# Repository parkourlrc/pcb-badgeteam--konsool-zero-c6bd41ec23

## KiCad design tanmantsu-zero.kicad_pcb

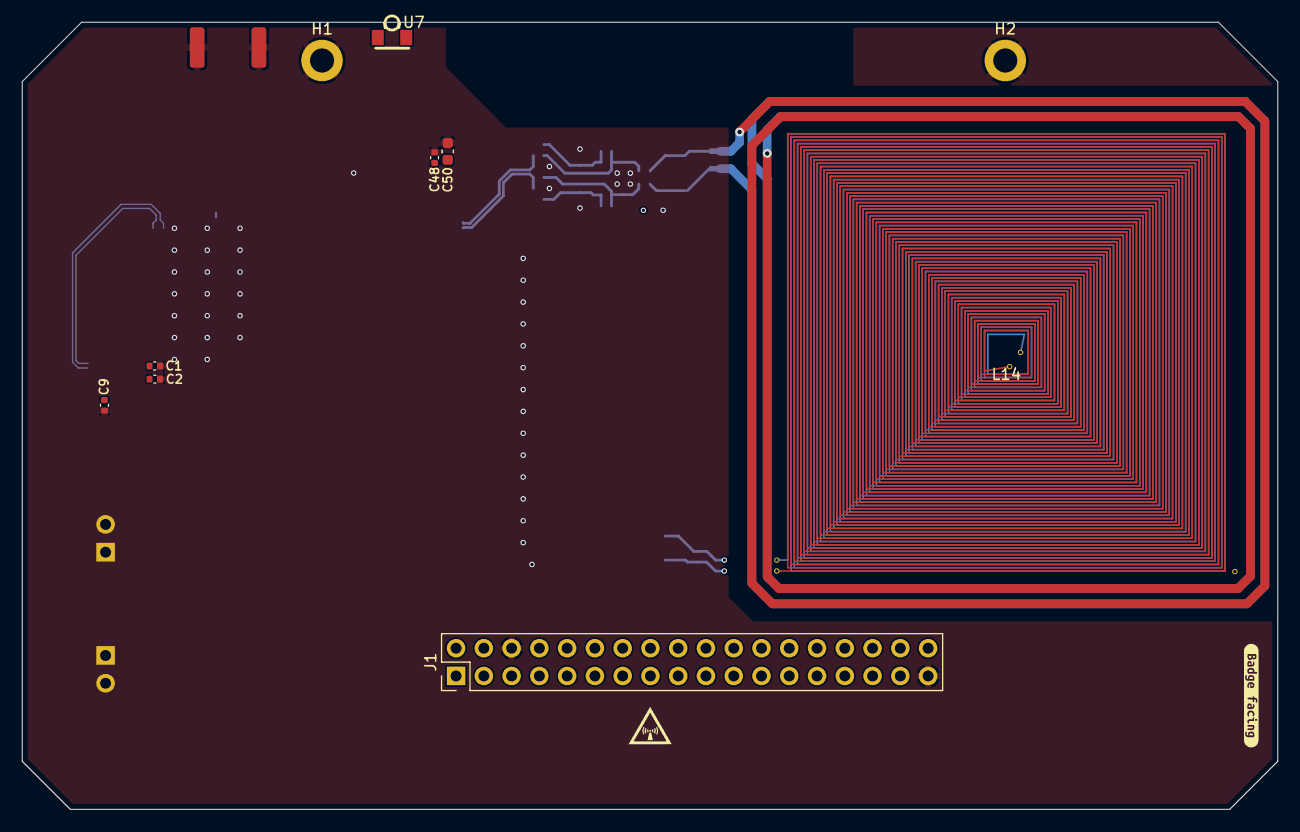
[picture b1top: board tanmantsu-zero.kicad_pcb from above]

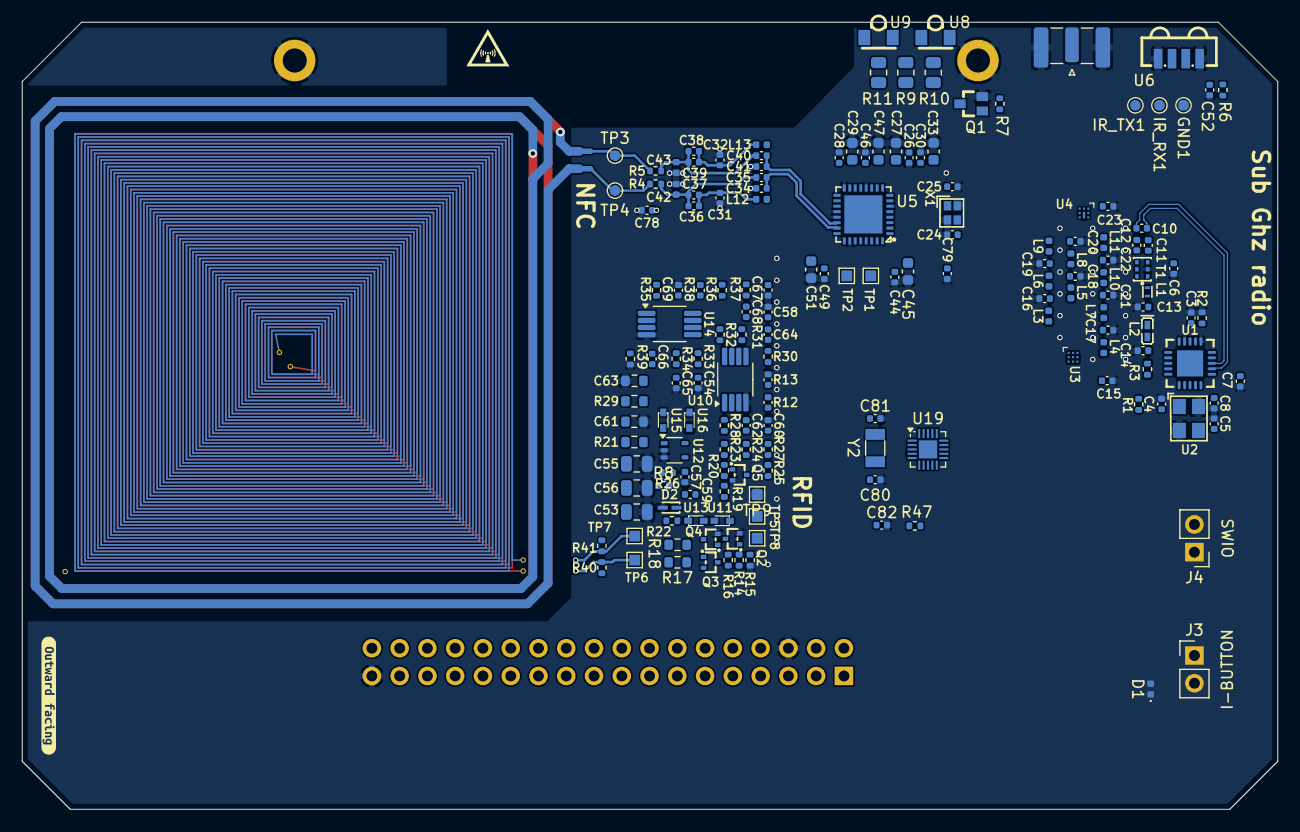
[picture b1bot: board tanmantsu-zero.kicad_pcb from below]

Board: 4 copper layers, 114.8 x 72.0 mm, 182 parts (169 on the bottom side), 105 nets.

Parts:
C1, C2, C3, C6, C7, C8, C9, C52, C54, C57, C58: 100nF; C_0402_1005Metric
C4, C5: 9pF; C_0402_1005Metric
C10: 0.6pF; C_0402_1005Metric
C11, C12, C34, C36, C38, C41, C66, C68, C69: 100pF; C_0402_1005Metric
C13: ??; C_0402_1005Metric
C14: 1.2pF; C_0402_1005Metric
C15, C23, C26, C28, C30, C35, C37, C39, C40, C44, C46, C48, C49, C59, C78, C79: 10nF; C_0402_1005Metric
C16, C19, C20, C64: C_0402_1005Metric
C17, C21: 10pF; C_0402_1005Metric
C18: 8.2pF; C_0402_1005Metric
C22: 22pF; C_0402_1005Metric
C24, C25: 6pF; C_0402_1005Metric
C27, C29, C33, C45, C47, C50, C51: 2.2uF; C_0603_1608Metric
C31, C32: 680pF; C_0402_1005Metric
C42, C43: 62pF; L_0402_1005Metric
C53: 3.9nF; C_0805_2012Metric
C55, C56: C_0805_2012Metric
C60: 1nF; C_0402_1005Metric
C61, C63: C_Small; R_0603_1608Metric
C62: 220nF; C_0402_1005Metric
C65, C67: 4.7nF; C_0402_1005Metric
C80, C81: 22p; C_0402_1005Metric
C82: 100n; C_0402_1005Metric
D1: D_TVS; D_0402_1005Metric
D2: MM5Z33; SOD-523_L1.2-W0.8-LS1.6-RD
GND1: TestPoint; TestPoint_Pad_D1.0mm
H1, H2: Mounting hole; MountingHole_2.2mm_M2_DIN965_Pad
IR_RX1: TestPoint; TestPoint_Pad_D1.0mm
IR_TX1: TestPoint; TestPoint_Pad_D1.0mm
J1: Internal Add-On; PinHeader_2x18_P2.54mm_Vertical
J2: LoRa; SMA_Samtec_SMA-J-P-H-ST-EM1_EdgeMount
J3, J4: Conn_01x02_Pin; PinHeader_1x02_P2.54mm_Vertical
L1: 3.3nH; IND-SMD_L1.0-W0.5
L2: LQG15HS6N8J02D; L0402-RD
L3, L4, L5, L6, L10: 0nH; L_0402_1005Metric
L7: 27nH; L_0402_1005Metric
L8: 2.7nH; L_0402_1005Metric
L9: 56nH; L_0402_1005Metric
L11: 22nH; L_0402_1005Metric
L12, L13: 270nH; L_0402_1005Metric
L14: 400mH; 61-42-rfid-coil
N1, N1#2: Radio-logo; radio-logo
N2: Housing; boards-guide
NT1, NT2: NetTie_2; NetTie-2_SMD_Pad0.5mm
Q1: DMN2058UW-7; SOT-323-3_L2.2-W1.3-P1.30-LS2.1-BR
Q2, Q4: DMN2004TK-7; SOT-523-3_L1.6-W0.8-P1.00-LS1.6-BR
Q3: DMP2004TK-7; SOT-523-3_L1.6-W0.8-P1.00-LS1.6-BR
Q5: DMN5L06TK-7; SOT-523-3_L1.6-W0.8-P1.00-LS1.6-BR
R1, R25: 330; R_0402_1005Metric
R2: 56k; R_0402_1005Metric
R3, R4, R5, R22, R40, R41: 0; R_0402_1005Metric
R6: 10; R_0402_1005Metric
R7: 200; R_0402_1005Metric
R8, R15, R26, R33, R36, R47: 10k; R_0402_1005Metric
R9, R10, R11: 47; R_0805_2012Metric
R12, R13, R38: 33k; C_0402_1005Metric
R14, R23: 100; R_0402_1005Metric
R16, R30, R32, R34, R35, R37: 1k; R_0402_1005Metric
R17, R18: 4.7; R_0603_1608Metric
R19, R20: 220; R_0402_1005Metric
R21: 330k; R_0603_1608Metric
R24: 47k; R_0402_1005Metric
R27: 5.1k; R_0402_1005Metric
R28: 1M; R_0402_1005Metric
R29: 10; R_0603_1608Metric
R31: 4.7k; R_0402_1005Metric
R39: 20k; R_0402_1005Metric
T1: B0310J50100AHF; XFMR-SMD_6P-L2.1-W1.3-P0.65-BL
TP1, TP2: TestPoint; TestPoint_Pad_1.0x1.0mm
TP3, TP4: TestPoint; TestPoint_Pad_D1.0mm
TP5: IRQ; TestPoint_Pad_1.0x1.0mm
TP6: AR1; TestPoint_Pad_1.0x1.0mm
TP7: AR2; TestPoint_Pad_1.0x1.0mm
TP8: DET; TestPoint_Pad_1.0x1.0mm
TP9: GND; TestPoint_Pad_1.0x1.0mm
U1: CC1101RGPR; QFN-20_L4.0-W4.0-P0.5-TL-EP
U2: 27MHz; OSC-SMD_4P-L3.2-W2.5-BL
U3, U4: BGS13S4N9E6327XTSA1; TSNP-9_L1.1-W1.1-P0.40-BL
U5: ST25R3916-AQWT; VFQFPN-32_L5.0-W5.0-P0.50-TL-EP3.5
U6: TSOP75338TR; SENSOR-SMD_TSOP75238TR
U7, U8, U9: VSMY14940; LED-SMD_VSMY14940
U10, U14: LMV358; VSSOP-8_3x3mm_P0.65mm
U11, U13, U15, U16: 1N4148X-TP; SOD-523F_L1.2-W0.8-LS1.7-RD
U12: LMV331IDCKR; SOT-353_SC-70-5
U19: CH32V003F4U6; QFN-20-1EP_3x3mm_P0.4mm_EP1.65x1.65mm
X1: XRCGB27M120F3M00R0; CRYSTAL-SMD_4P-L2.0-W1.6-BL-B
Y2: 32.768KHz; Crystal_SMD_3215-2Pin_3.2x1.5mm
kibuzzard-672F417C: G***; kibuzzard-672F417C
kibuzzard-672F4776: G***; kibuzzard-672F4776

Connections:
+1.65V: R28.2, R30.1, U10.6 (-), U10.7, U14.3 (+), U14.5 (+)
+3.3V: C1.1, C3.1, C6.1, C7.1, C8.1, C9.1, C15.1, C23.1, C26.1, C27.1, C28.1, C29.1, C61.1, C78.1, C79.1, C82.1, J1.8, J1.33, R6.1, R9.1, R10.1, R11.1, R26.1, R29.1, R47.1, U1.4 (DVDD), U1.9 (AVDD), U1.11 (AVDD), U1.14 (AVDD), U1.15 (AVDD), U1.18 (DGUARD), U3.7 (VDD), U4.7 (VDD), U5.1 (VDD_IO), U5.8 (VDD), U5.10 (VDD_TX), U19.6 (VDD)
+3.3VA: C54.2, C57.2, C58.2, C63.1, R12.1, R29.2, U10.8 (V+), U12.5 (V+), U14.8 (V+), U15.1 (C)
+5V: Q3.3 (D), R16.1, R24.1
/NFC block/AGDC: C49.1, C51.1, U5.24 (AGDC)
/NFC block/RFI_N: C34.1, C35.2, U5.23 (RFI2)
/NFC block/RFI_P: C40.1, C41.2, U5.22 (RFI1)
/NFC block/RFO1: L12.1, U5.13 (RFO1)
/NFC block/RFO2: L13.1, U5.15 (EFO2)
/NFC block/VDD_A: C30.1, C33.1, U5.7 (VDD_A)
/NFC block/VDD_AM: C48.1, C50.1, U5.11 (VDD_AM)
/NFC block/VDD_D: C44.1, C45.1, U5.3 (VDD_D)
/NFC block/VDD_DR: C46.1, C47.1, U5.9 (VDD_RF), U5.14 (VDD_DR)
/sub-GHz-radio/Antenna balance/ANT_OUT: J2.1 (In), U4.4 (RFin)
/sub-GHz-radio/Antenna balance/RF_IN: R3.2, U3.4 (RFin)
/sub-GHz-radio/RF-Balance/RF_N: C10.1, C11.1, U1.13 (RF_N)
/sub-GHz-radio/RF-Balance/RF_P: C10.2, C12.1, U1.12 (RF_P)
E0: J1.11, U1.3 (GDO2)
E1: J1.12, R1.1
E3: J1.14, U5.29 (BSS)
E4: J1.15, J4.2, R47.2, U19.15 (PD1)
E9: IR_RX1.1, J1.25, U6.3 (OUT)
E10: IR_TX1.1, J1.23, R7.1
GND: C1.2, C2.1, C3.2, C4.2, C5.2, C6.2, C7.2, C8.2, C9.2, C13.2, C14.2, C15.2, C16.1, C17.2, C18.2, C19.1, C20.2, C21.2, C22.2, C23.2, C24.2, C25.1, C26.2, C27.2, C28.2, C29.2, C30.2, C31.2, C32.1, C33.2, C34.2, C41.1, C42.2, C43.1, C44.2, C45.2, C46.2, C47.2, C48.2, C49.2, C50.2, C51.2, C52.2, C53.2, C54.1, C55.2, C56.2, C57.1, C58.1, C60.2, C61.2, C63.2, C65.2, C67.2, C69.1, C78.2, C79.2, C80.2, C81.2, C82.2, D1.1 (A1), D2.2 (A), GND1.1, H1.1, H2.1, J1.6, J1.35, J2.2 (Ext), J3.1, J4.1, Q1.2 (S), Q2.2 (S), Q4.2 (S), Q5.2 (S), R2.1, R8.2, R13.2, R15.2, R39.2, T1.2 (GND), TP9.1, U1.16 (GND), U1.19 (GND), U1.21 (EP), U2.2 (GND), U2.4 (GND), U3.6 (DGND), U3.9 (GND), U4.6 (DGND), U4.9 (GND), U5.6 (GND_D), U5.12 (GND_DR), U5.16 (GND_DR), U5.20 (I2C_EN), U5.21 (VSS), U5.26 (GND_A), U6.1 (GND), U6.4 (GND), U10.4 (V-), U12.2 (V-), U12.3 (-), U14.4 (V-), U16.1 (C), U19.4 (VSS), U19.21 (VSS), X1.2 (GND), X1.4 (GND)
IBTN: D1.2 (A2), J3.2, R23.1
INT_SCL: J1.9, U19.9 (PC2)
INT_SDA: J1.10, U19.8 (PC1)
NFC_ANT: NT1.2, NT2.1
NFC_IRQ: TP5.1, U5.27 (IRQ), U11.2 (A), U19.20 (PD6)
unnamed: C11.2, T1.3 (Balanced)
unnamed: C12.2, T1.4 (Balanced)
unnamed: C13.1, L1.2, L2.1
unnamed: C14.1, L2.2, R3.1
unnamed: C16.2, L3.2, L6.1
unnamed: C17.1, L4.2, L7.1
unnamed: C18.1, L5.2, L8.1
unnamed: C19.2, L6.2, L9.1
unnamed: C21.1, L7.2, L10.1
unnamed: C22.1, L10.2, L11.1
unnamed: C31.1, C36.1, C37.2, L12.2
unnamed: C32.2, C38.2, C39.2, L13.2
unnamed: C35.1, C36.2, C37.1, C42.1, R4.1
unnamed: C38.1, C39.1, C40.2, C43.2, R5.1
unnamed: C53.1, C55.1, C56.1, R21.1, R22.1, R41.1
unnamed: C59.2, R23.2, R24.2
unnamed: C60.1, C62.1, R27.2
unnamed: C64.2, R31.2, R32.1, U10.1
unnamed: C65.1, R32.2, R33.2, R34.2
unnamed: C66.2, R33.1, R35.1, U14.1
unnamed: C67.1, R35.2, R36.2, R37.2
unnamed: C68.2, R36.1, R38.1, U14.7
unnamed: C59.1, D2.1 (K), R25.2, R27.1, TP8.1, U13.1 (C)
unnamed: L14.1, R40.1, TP6.1
unnamed: L14.2, R41.2, TP7.1
unnamed: NT1.1, R5.2, TP4.1
unnamed: NT2.2, R4.2, TP3.1
unnamed: Q1.3 (D), U7.1 (C), U8.1 (C), U9.1 (C)
unnamed: Q1.1 (G), R7.2, R8.1
unnamed: Q2.3 (D), Q3.1 (G), Q4.1 (G), R16.2
unnamed: Q2.1 (G), R14.2, R15.1
unnamed: Q3.2 (S), R17.1
unnamed: Q4.3 (D), R18.2
unnamed: Q5.3 (D), R25.1
unnamed: Q5.1 (G), R20.2
unnamed: R17.2, R18.1, R40.2
unnamed: L1.1, T1.1 (Unbalanced)
unnamed: C2.2, U1.5 (DCOUPL)
unnamed: R1.2, U1.6 (GDO0(ATEST))
unnamed: R2.2, U1.17 (RBIAS)
unnamed: C4.1, U1.8 (XOSC_Q1), U2.1
unnamed: C5.1, U1.10 (XOSC_Q2), U2.3
unnamed: L3.1, U3.3 (RF1)
unnamed: L4.1, U3.5 (RF2)
unnamed: L5.1, U3.2 (RF3)
unnamed: L9.2, U4.3 (RF1)
unnamed: L11.2, U4.5 (RF2)
unnamed: C20.1, L8.2, U4.2 (RF3)
unnamed: TP2.1, U5.25 (CSI)
unnamed: TP1.1, U5.2 (CSO)
unnamed: C25.2, U5.5 (XTI), X1.1
unnamed: C24.1, U5.4 (XTO), X1.3
unnamed: C52.1, R6.2, U6.2 (+VS)
unnamed: R9.2, U7.2 (A)
unnamed: R10.2, U8.2 (A)
unnamed: R11.2, U9.2 (A)
unnamed: C62.2, R28.1, U10.3 (+), U15.2 (A), U16.2 (A)
unnamed: C64.1, R30.2, R31.1, U10.2 (-)
unnamed: R12.2, R13.1, U10.5 (+)
unnamed: R19.2, R20.1, U11.1 (C)
unnamed: R21.2, U12.1 (+)
unnamed: R22.2, U13.2 (A)
unnamed: C66.1, R34.1, U14.2 (-)
unnamed: C68.1, R37.1, U14.6 (-)
unnamed: C81.1, U19.2 (PA1), Y2.1
unnamed: C80.1, U19.3 (PA2), Y2.2
RFID_CARRIER: R26.2, U12.4, U19.13 (PC6)
RFID_IN: R14.1, U19.14 (PC7)
RFID_PULL: R19.1, U19.18 (PD4)
RFID_RF_OUT: C69.2, R38.2, R39.1, U19.19 (PD5)
RF_SW_0: U3.1 (V1), U4.1 (V1), U19.17 (PD3)
RF_SW_1: U3.8 (V2), U4.8 (V2), U19.16 (PD2)
SPI_CMD: J1.16, U1.20 (SI), U5.31 (MOSI)
SPI_D0: J1.18, U1.2 (SO(GDO1)), U5.32 (MISO/SDA)
SPI_D3: J1.21, U1.7 (CSn)
SPI_SCK: J1.17, U1.1 (SCLK), U5.30 (SCLK/SCL)

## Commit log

2024-12-17 Add WIP NFC schematic.
2024-12-18 Placed NFC components roughly
2024-12-25 Add more of the RFID schematic, moved stuff around on the board.
2025-01-06 Moved coil to the side, increased PCB area, added MCU.
2025-01-07 Add RFID write line to ch32v003
2025-03-22 board elements that were missing.
